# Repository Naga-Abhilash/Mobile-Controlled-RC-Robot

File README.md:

# Mobile-Controlled-RC-Robot

I Developed a Remote Controlled car (RC) with dedicated PCB and controlled it from custom built mobile application that could be used for surveillance.
•	Designed the PCB in eagle and incorporated micro controller (ATmega 328), crystal oscillator, resistors and capacitors into the PCB.
•	Developed the mobile application in MIT App inventor 2 and incorporated Bluetooth module to enable the user to control the robot and move it in particular directions up to a range of 15m.
•	Achieved a precision rate of 30% more in control and cost efficiency of 40% when compared to IR based products available in market.

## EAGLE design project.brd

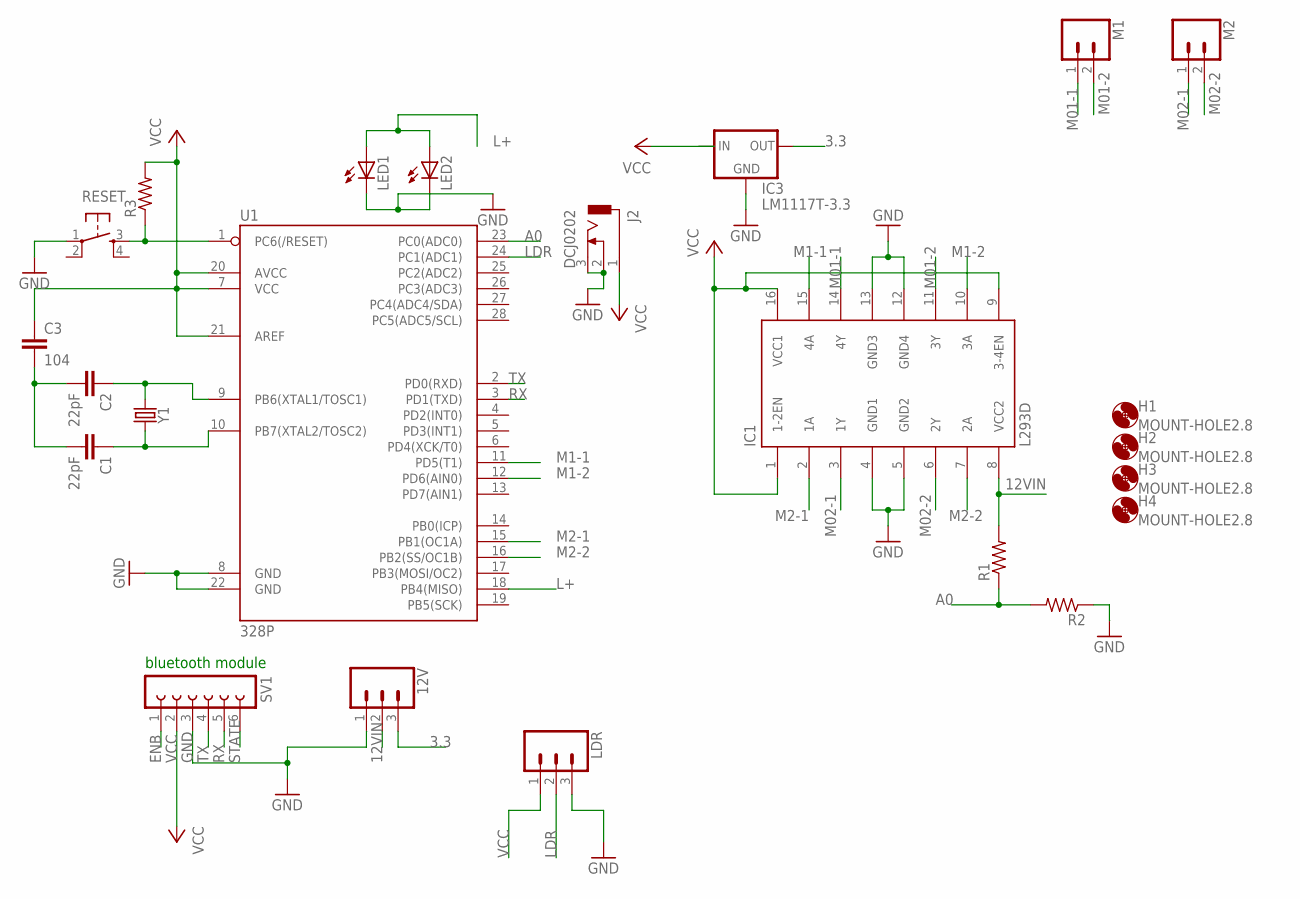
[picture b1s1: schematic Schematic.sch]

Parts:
12V: CONN_03; 1X03
C1, C2: 22pF; CAP-PTH-2.54
C3: 104; CAP-PTH-2.54
H1, H2, H3, H4: MOUNT-HOLE2.8; 2,8
IC1: L293D; DIL16
IC3: LM1117T-3.3; TO220
J2: DCJ0202
LDR: CONN_03; 1X03
LED1, LED2: LED5MM
M1, M2: CONN_023.5MM; SCREWTERMINAL-3.5MM-2
R1, R2, R3: R-US_0204/7; 0204/7
RESET: TAC_SWITCHPTH; TACTILE-PTH
SV1: FE06-1; FE06
U1: 328P; DIP28
Y1: CRYSTALPTH-HC49US; HC49US

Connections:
3.3: 12V.3, IC3.2 (OUT)
12VIN: 12V.2, IC1.8 (VCC2), R1.2
A0: R1.1, R2.2, U1.23 (PC0(ADC0))
ENB: SV1.1
GND: 12V.1, IC1.4 (GND1), IC1.5 (GND2), IC1.12 (GND4), IC1.13 (GND3), IC3.1 (GND), J2.2, J2.3, LDR.3, LED1.K (C), LED2.K (C), R2.1, RESET.1, SV1.3, U1.8 (GND), U1.22 (GND)
L+: LED1.A, LED2.A, U1.18 (PB4(MISO))
LDR: LDR.2, U1.24 (PC1(ADC1))
M1-1: IC1.15 (4A), U1.11 (PD5(T1))
M01-1: IC1.14 (4Y), M1.1
M1-2: IC1.10 (3A), U1.12 (PD6(AIN0))
M01-2: IC1.11 (3Y), M1.2
M02-1: IC1.3 (1Y), M2.1
M2-1: IC1.2 (1A), U1.15 (PB1(OC1A))
M02-2: IC1.6 (2Y), M2.2
M2-2: IC1.7 (2A), U1.16 (PB2(SS/OC1B))
unnamed: C2.1, U1.9 (PB6(XTAL1/TOSC1)), Y1.1
unnamed: C1.1, U1.10 (PB7(XTAL2/TOSC2)), Y1.2
unnamed: C1.2, C2.2, C3.2
unnamed: R3.1, RESET.3, U1.1 (PC6(/RESET))
RX: SV1.5, U1.3 (PD1(TXD))
STATE: SV1.6
TX: SV1.4, U1.2 (PD0(RXD))
VCC: C3.1, IC1.1 (1-2EN), IC1.9 (3-4EN), IC1.16 (VCC1), IC3.3 (IN), J2.1, LDR.1, R3.2, SV1.2, U1.7 (VCC), U1.20 (AVCC), U1.21 (AREF)

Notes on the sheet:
bluetooth module

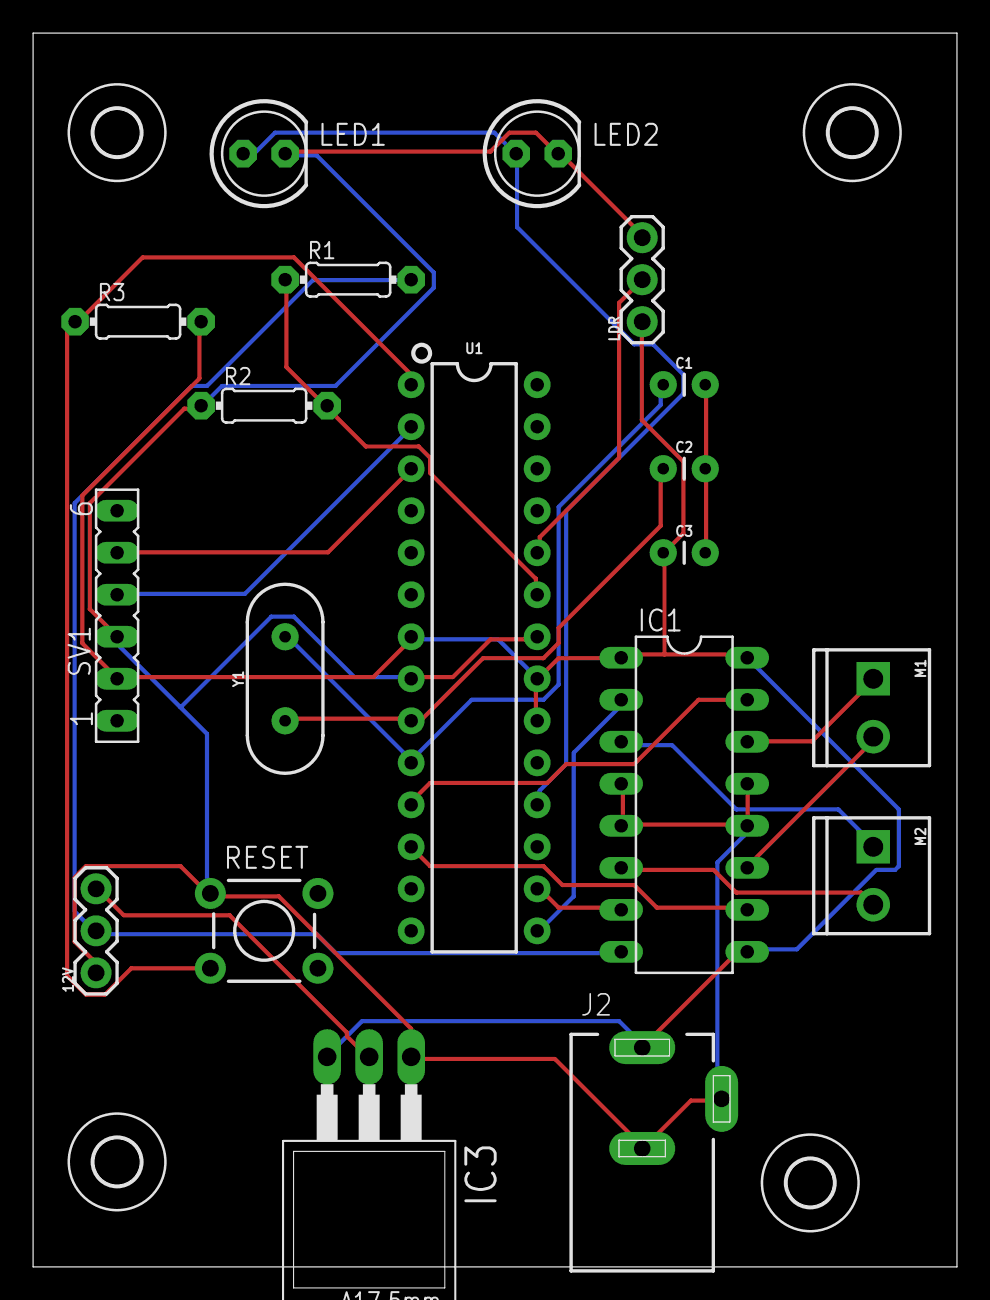
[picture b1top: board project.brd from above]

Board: 2 copper layers, 55.9 x 74.6 mm, 23 parts (0 on the bottom side), 21 nets.

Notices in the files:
parts and their libraries:
SparkFun-IC-Microcontroller: Licensing: Creative Commons ShareAlike 4.0 International - https://creativecommons.org/licenses/by-sa/4.0
